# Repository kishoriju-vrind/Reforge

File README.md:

<div align="center">

# Reforge

**Custom FPGA Development Board & ESP32 Host System**

## **FRONT**

## **BACK**

</div>

## Table of Contents
* [About the Project](#about-the-project)
  * [Aim](#aim)
  * [Description](#description)
  * [Tech-Stack](#tech-stack)
* [File Structure](#file-structure)
* [Getting Started](#getting-started)
* [Usage](#usage)
  * [1. iCE40 FPGA Graphics Demo](#1-ice40-fpga-graphics-demo)
  * [2. ESP32 Host Firmware](#2-esp32-host-firmware)

---

## About the Project

### Aim
Designing a custom PCB development board that combines an ESP32 microcontroller and an iCE40 FPGA to understand how microcontrollers and FPGAs interact in real embedded systems.

### Description
Instead of relying on fixed hardware, FPGAs allow for custom hardware configurations. In this project, the **ESP32** acts as the host system. It is responsible for storing FPGA designs in its filesystem and loading them directly onto the **iCE40 FPGA** when needed. The two chips communicate via SPI, allowing the ESP32 to send data and control the FPGA dynamically. 

The current hardware prototype includes a custom VGA output implementation, where the FPGA acts as a hardwired video card rendering horizontal RGB color bands in real-time.

### Tech-Stack
* **Languages:** Embedded C (ESP32), Verilog HDL (FPGA)
* **Tools:** ESP-IDF, OSS CAD Suite (Yosys, NextPNR), KiCAD
* **Protocols:** SPI (Inter-chip communication), VGA (Analog Video),OTA 

---

## File Structure

```text
Reforge
├── ESP32E                  # ESP32 source code and firmware
│   └── OTA                 # Host system and file management
│       ├── main            # Core C files (SPI communication, FPGA config)
│       ├── CMakeLists.txt  # Build configuration
│       └── partitions.csv  # Custom memory partitions for bitstream storage
        └── README.md  
├── ICE40                   # FPGA hardware designs in Verilog
│   ├── blink               # Basic LED blink and SPI test
        ├── blink.v           # Verilog logic for horizontal RGB bands
│       ├── pins.pcf        # FPGA pinout mapping
│       ├── build.bat       # Automated synthesis script
│       └── flash.bat       # Automated flashing script
│   └── VGA                 # Custom hardware VGA generator
│       ├── vga.v           # Verilog logic for horizontal RGB bands
│       ├── pins.pcf        # FPGA pinout mapping
│       ├── build.bat       # Automated synthesis script
│       └── flash.bat       # Automated flashing script
├── KICAD                   # Schematics for the custom development board
│   ├── Reforge.kicad_sch
│   └── Reforge.kicad_pcb
└── README.md
```
## Getting Started

### Installation

Clone the repository:

```bash
git clone https://github.com/kishorju-vrind/Reforge.git
cd Reforge
```

## System Architecture & Modules

The project is divided into different functional modules. Each module handles a specific part of the system.

- **FPGA Configuration Manager:** Stores multiple FPGA designs on the ESP32 and loads them onto the iCE40 FPGA.
- **ESP32-iCE40 SPI Communication:** Handles data transfer and control between the ESP32 and iCE40 FPGA using SPI.
- **Over-The-Air (OTA) Updates:** Allows new bitstreams and firmware to be downloaded remotely over Wi-Fi.
- **Bitstream Transfer & CRC Check:** Transfers the FPGA configuration file in parts and checks the data for errors during transfer.
- **Wireless Design Selection:** Allows the user to select and load the required FPGA design remotely.

## Usage

The following steps explain how to build and run the different parts of the project.

### 1. OTA

Go to the OTA directory:

```bash
cd ESP32/OTA
```

Enter your Wi-Fi SSID and password in the required fields in the code:

```
#define WIFI_SSID "Your_SSID"
#define WIFI_PASS "Your_Password"
```
Build the project using ESP-IDF:
```
idf.py fullclean
idf.py build
```

Flash the firmware and open the serial monitor:
```
idf.py flash monitor
```

### 2.FPGA Configuration
Open the required FPGA project from the FPGA folder.
Build the Verilog design using the provided build script:
```
build.bat
```
After building, flash the generated bitstream to the iCE40 FPGA using:
```
flash.bat
```

### 3. ESP32-ICE40 SPI Communication
Open the SPI communication project from the ESP32 folder.
Build and flash the ESP32 code using:
```
idf.py build flash monitor
```
The ESP32 then communicates with the iCE40 FPGA through SPI.

### 4. bitstream Transfer and CRC Check

Run the ESP32 firmware and start the firmware/bitstream transfer.
The bitstream is transferred in smaller parts and the CRC check is used to verify the received data.
## Results
The schematic and design for the custom PCB was completed. The main communication and FPGA related functions were also tested separately.

The following results were achieved:

- ESP32-E to ESP32-E communication
- OTA communication and wireless FPGA configuration
- VGA output using the iCE40 (UPduino) FPGA

## Contributors

* [Suraj Giri](https://github.com/kishorju-vrind)
* [Amrit Tiwari](https://github.com/amrit-reboot)

## Mentors

* [Archit More](https://github.com/avm1234567)
* [Harshit Bhalani](https://github.com/harshit6-b)

## Resources

- [Generating VGA with an FPGA](https://blog.waynejohnson.net/doku.php/generating_vga_with_an_fpga)
- [FPGA and VGA Tutorial](https://youtu.be/FlkNgJXEyrc?si=HfDX1ZITgR_oPYt3)
- [FPGA Tutorial](https://www.youtube.com/watch?v=yLNWu6AxftI)
- [FPGA Learning Playlist](https://youtube.com/playlist?list=PLEBQazB0HUyQ5YJSdCBb79orXaR3Uk5vm&si=PIlAy49dysh-u-zc)
- [HDLBits Problem Sets](https://hdlbits.01xz.net/wiki/Problem_sets)
- [ESP-IDF File System Documentation](https://docs.espressif.com/projects/esp-idf/en/stable/esp32/api-guides/file-system-considerations.html)
- [ESP32 Tutorial](https://youtu.be/MCi7dCBhVpQ?si=dbMR7HTboAvRNwoI)
- [Shrike Documentation](https://vicharak-in.github.io/shrike/index.html)

## Acknowledgements

We are grateful to our mentors – **Harshit Bhalani** and **Archit More** – for their guidance and support throughout the course of this project.

We also thank [SRA-VJTI](https://sravjti.in/) for their support in organizing [Eklavya 2026](https://eklavya.sravjti.in/) and for providing us the opportunity to work on this project.

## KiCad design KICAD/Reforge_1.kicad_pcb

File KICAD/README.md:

THIS FOLDER IS MEANT TO STORE THE PCB DESIGNS, MADE ON KICAD 10.0

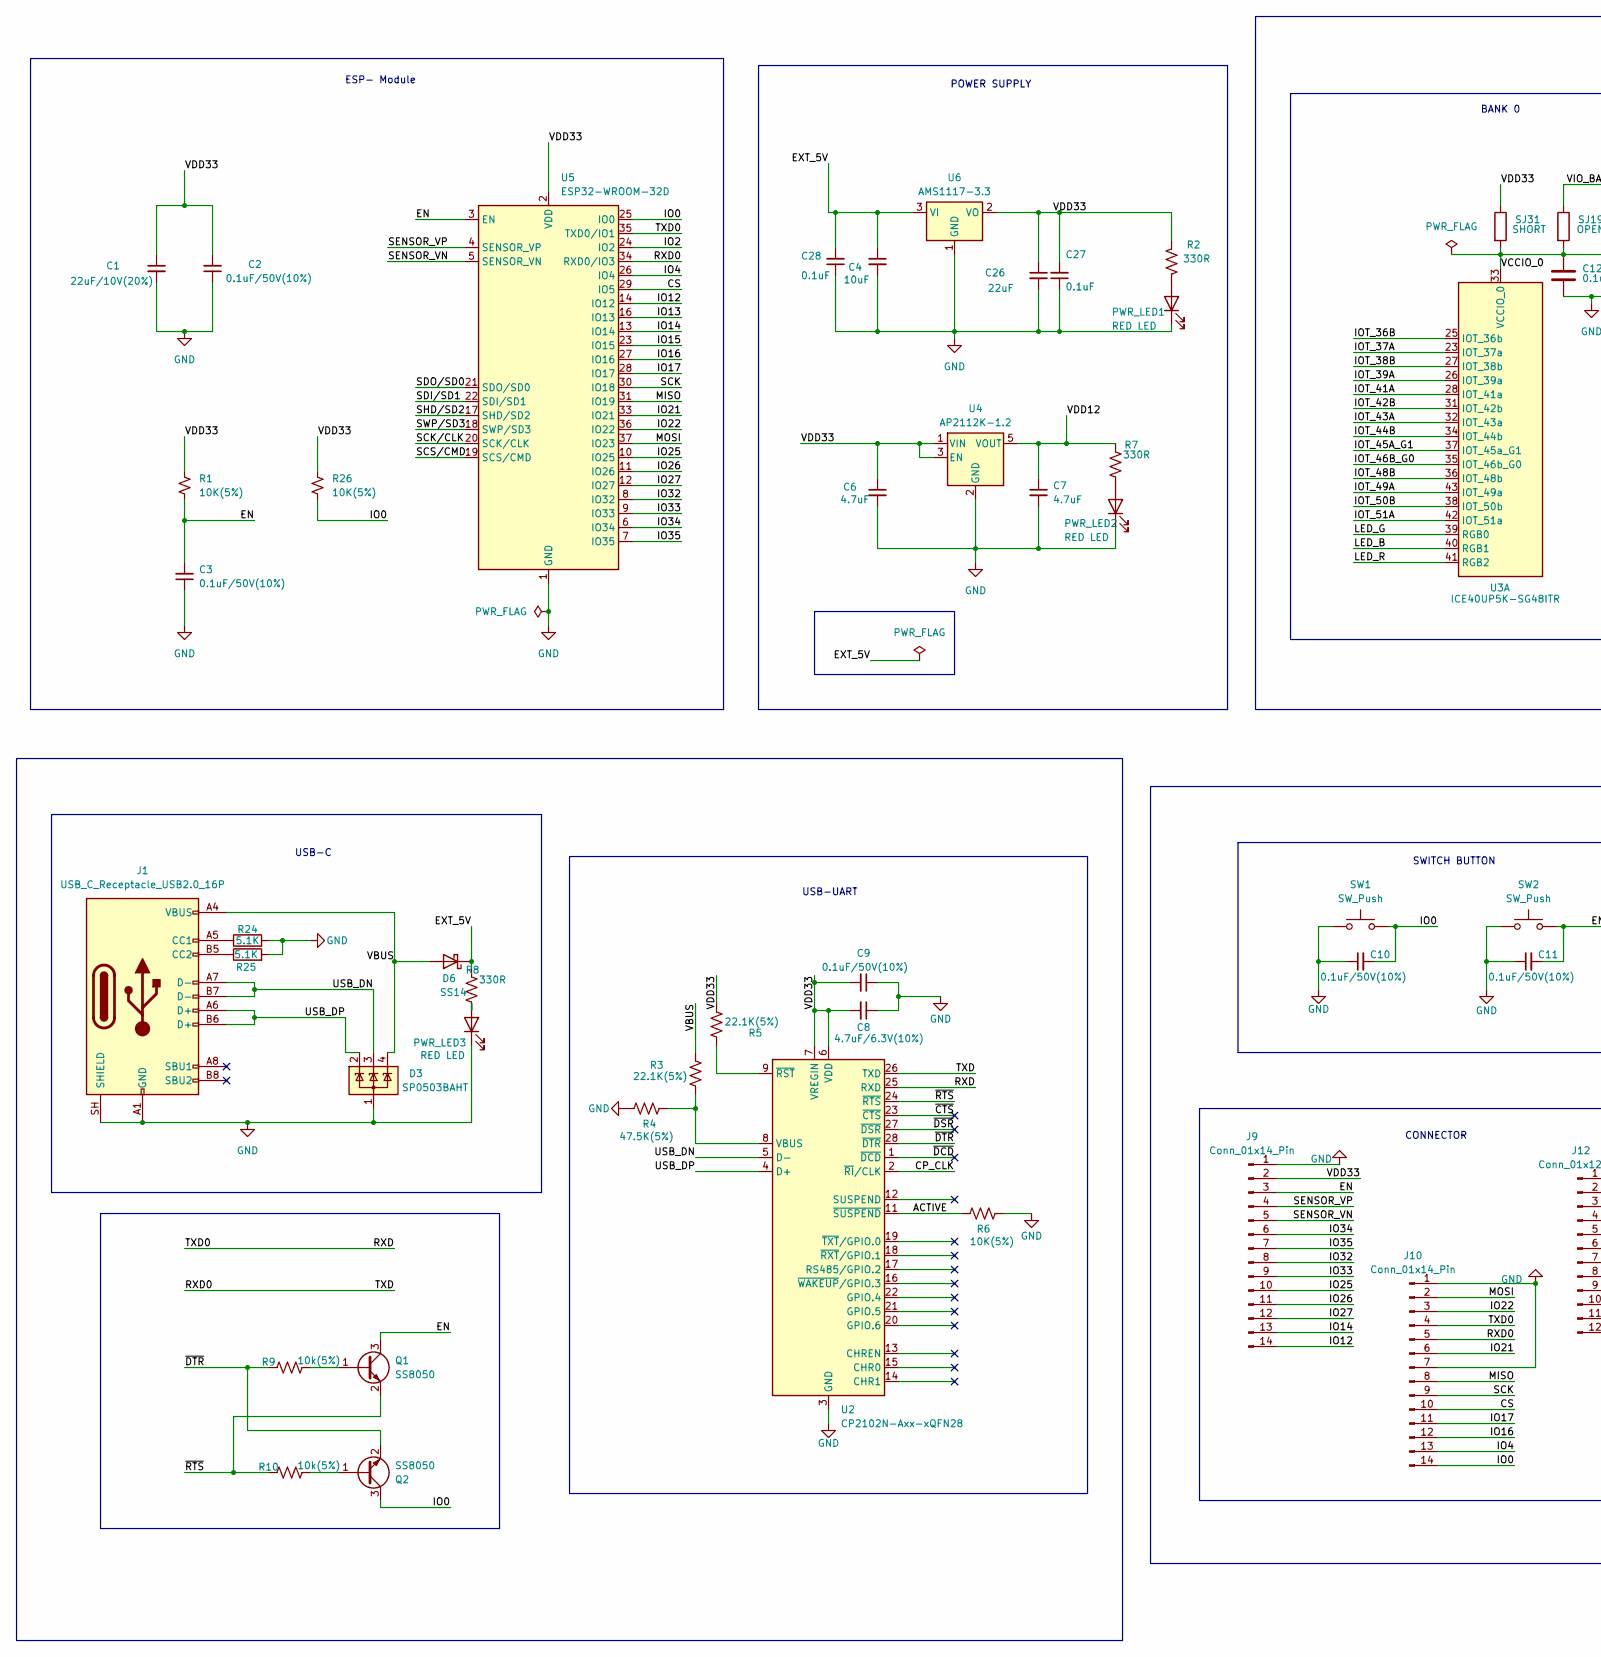
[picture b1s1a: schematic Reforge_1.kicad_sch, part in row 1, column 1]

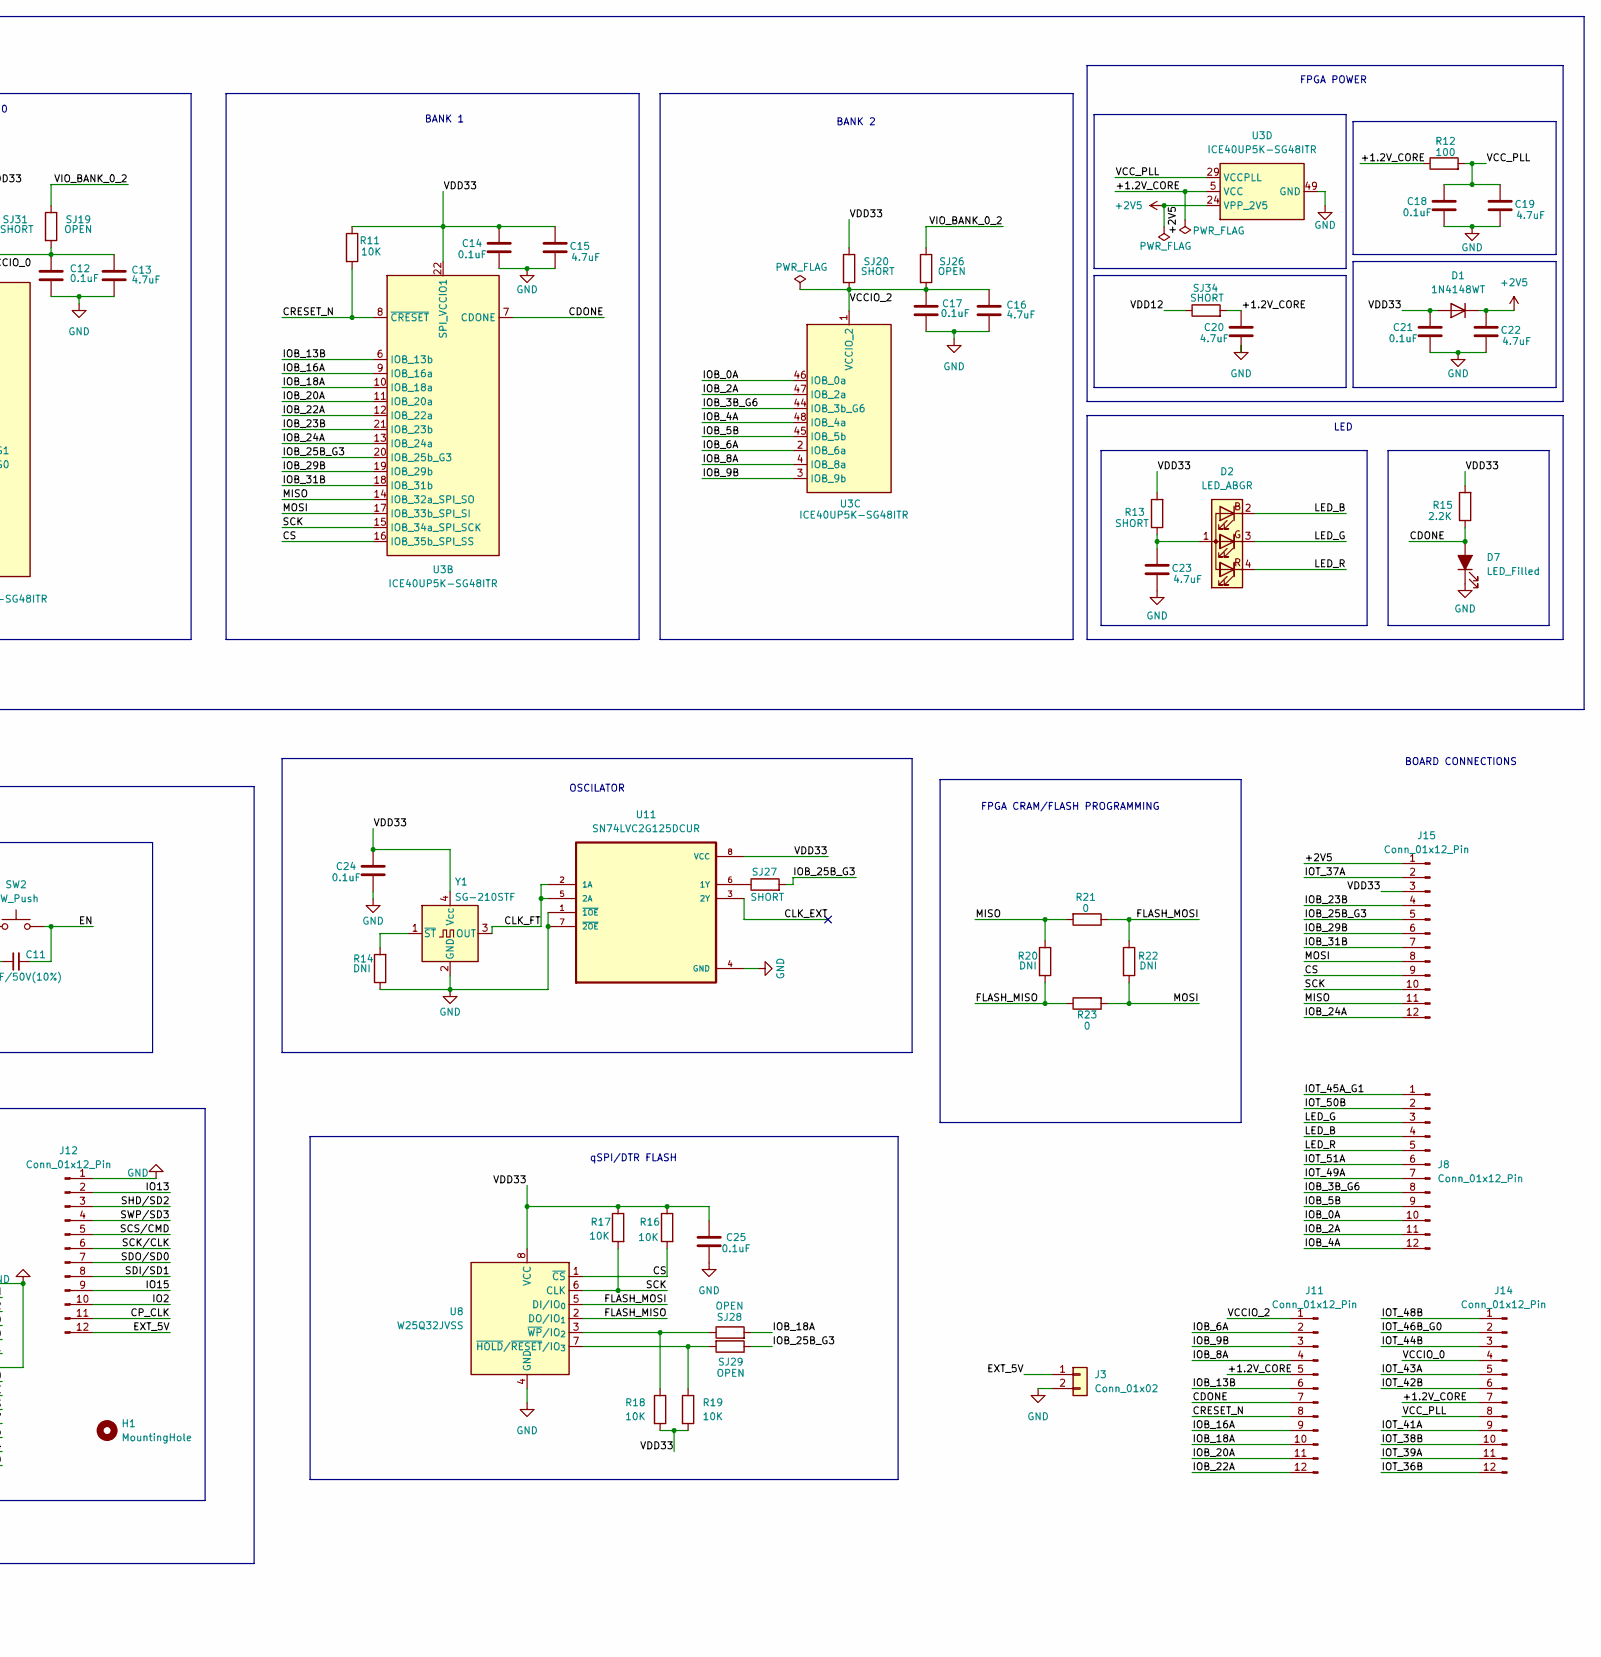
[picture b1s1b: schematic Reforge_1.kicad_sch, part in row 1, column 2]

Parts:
C1: 22uF/10V(20%); C_0805_2012Metric
C2, C3, C9, C10, C11: 0.1uF/50V(10%); C_0805_2012Metric
C4: 10uF; C_0805_2012Metric
C6, C7, C13, C15, C16, C19, C20, C22, C23: 4.7uF; C_0805_2012Metric
C8: 4.7uF/6.3V(10%); C_0805_2012Metric
C12, C14, C17, C18, C21, C24, C25, C27, C28: 0.1uF; C_0805_2012Metric
C26: 22uF; C_0805_2012Metric
D1: 1N4148WT; D_SOD-523
D2: LED_ABGR; LED_RGB_Wuerth-PLCC4_3.2x2.8mm_150141M173100
D3: SP0503BAHT; SOT-143
D6: SS14; D_SMB
D7: LED_Filled; LED_0603_1608Metric
H1: MountingHole; MountingHole_2.1mm
J1: USB_C_Receptacle_USB2.0_16P; USB_C_Receptacle_GCT_USB4105-xx-A_16P_TopMnt_Horizontal
J3: Conn_01x02; PinHeader_1x02_P2.54mm_Vertical
J8, J11, J12, J14, J15: Conn_01x12_Pin; PinHeader_1x12_P2.54mm_Vertical
J9, J10: Conn_01x14_Pin; PinHeader_1x14_P2.54mm_Vertical
PWR_LED1, PWR_LED2, PWR_LED3: RED LED; LED_0603_1608Metric
Q1, Q2: SS8050; SOT-23
R1, R6, R26: 10K(5%); R_0805_2012Metric_Pad1.20x1.40mm_HandSolder
R2, R7, R8: 330R; R_0805_2012Metric_Pad1.20x1.40mm_HandSolder
R3, R5: 22.1K(5%); R_0805_2012Metric_Pad1.20x1.40mm_HandSolder
R4: 47.5K(5%); R_0805_2012Metric_Pad1.20x1.40mm_HandSolder
R9, R10: 10k(5%); R_0805_2012Metric_Pad1.20x1.40mm_HandSolder
R11, R16, R17, R18, R19: 10K; R_0805_2012Metric_Pad1.20x1.40mm_HandSolder
R12: 100; R_0805_2012Metric_Pad1.20x1.40mm_HandSolder
R13: SHORT; SolderJumper-2_P1.3mm_Open_Pad1.0x1.5mm
R14, R20, R22: DNI; R_0805_2012Metric_Pad1.20x1.40mm_HandSolder
R15: 2.2K; R_0805_2012Metric_Pad1.20x1.40mm_HandSolder
R21, R23: 0; R_0805_2012Metric_Pad1.20x1.40mm_HandSolder
R24, R25: 5.1K; R_0805_2012Metric_Pad1.20x1.40mm_HandSolder
SJ19, SJ26, SJ28, SJ29: OPEN; SolderJumper-2_P1.3mm_Open_Pad1.0x1.5mm
SJ20, SJ31, SJ34: SHORT; SolderJumper-2_P1.3mm_Bridged2Bar_Pad1.0x1.5mm
SJ27: SHORT; SolderJumper-2_P1.3mm_Open_Pad1.0x1.5mm
SW1, SW2: SW_Push; SW_Push_SPST_NO_Alps_SKRK
U2: CP2102N-Axx-xQFN28; QFN-28-1EP_5x5mm_P0.5mm_EP3.35x3.35mm
U3: ICE40UP5K-SG48ITR; QFN-48-1EP_7x7mm_P0.5mm_EP5.6x5.6mm
U4: AP2112K-1.2; SOT-23-5
U5: ESP32-WROOM-32D
U6: AMS1117-3.3; SOT-223-3_TabPin2
U8: W25Q32JVSS; SOIC-8_5.3x5.3mm_P1.27mm
U11: SN74LVC2G125DCUR; SOP50P310X90-8N
Y1: SG-210STF; Oscillator_SMD_SeikoEpson_SG210-4Pin_2.5x2.0mm

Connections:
+2V5: C22.1, D1.1 (K), J15.1, U3.24 (VPP_2V5)
/+1.2V_CORE: C20.1, J11.5, J14.7, R12.1, SJ34.2, U3.5 (VCC), U3.30 (VCC)
/ACTIVE: R6.1, U2.11 (~SUSPEND)
/CDONE: D7.2 (A), J11.7, R15.1, U3.7 (CDONE)
/CLK_EXT: U11.3 (2Y)
/CLK_FT: U11.2 (1A), U11.5 (2A), Y1.3 (OUT)
/CP_CLK: J12.11, U2.2 (~RI/CLK)
/CRESET_N: J11.8, R11.2, U3.8 (~CRESET)
/CS: J10.10, J15.9, R16.2, U3.16 (IOB_35b_SPI_SS), U5.29 (IO5), U8.1 (~CS)
/EN: C3.2, C11.2, J9.3, Q1.3 (C), R1.2, SW2.2, U5.3 (EN)
/EXT_5V: C4.1, C28.2, D6.1 (K), J3.1, J12.12, R8.1, U6.3 (VI)
/FLASH_MISO: R20.2, R23.1, U8.2 (DO/IO_{1})
/FLASH_MOSI: R21.1, R22.1, U8.5 (DI/IO_{0})
/IO0: C10.2, J10.14, Q2.3 (C), R26.2, SW1.2, U5.25 (IO0)
/IO2: J12.10, U5.24 (IO2)
/IO4: J10.13, U5.26 (IO4)
/IO12: J9.14, U5.14 (IO12)
/IO13: J12.2, U5.16 (IO13)
/IO14: J9.13, U5.13 (IO14)
/IO15: J12.9, U5.23 (IO15)
/IO16: J10.12, U5.27 (IO16)
/IO17: J10.11, U5.28 (IO17)
/IO21: J10.6, U5.33 (IO21)
/IO22: J10.3, U5.36 (IO22)
/IO25: J9.10, U5.10 (IO25)
/IO26: J9.11, U5.11 (IO26)
/IO27: J9.12, U5.12 (IO27)
/IO32: J9.8, U5.8 (IO32)
/IO33: J9.9, U5.9 (IO33)
/IO34: J9.6, U5.6 (IO34)
/IO35: J9.7, U5.7 (IO35)
/IOB_0A: J8.10, U3.46 (IOB_0a)
/IOB_2A: J8.11, U3.47 (IOB_2a)
/IOB_3B_G6: J8.8, U3.44 (IOB_3b_G6)
/IOB_4A: J8.12, U3.48 (IOB_4a)
/IOB_5B: J8.9, U3.45 (IOB_5b)
/IOB_6A: J11.2, U3.2 (IOB_6a)
/IOB_8A: J11.4, U3.4 (IOB_8a)
/IOB_9B: J11.3, U3.3 (IOB_9b)
/IOB_13B: J11.6, U3.6 (IOB_13b)
/IOB_16A: J11.9, U3.9 (IOB_16a)
/IOB_18A: J11.10, SJ28.2, U3.10 (IOB_18a)
/IOB_20A: J11.11, U3.11 (IOB_20a)
/IOB_22A: J11.12, U3.12 (IOB_22a)
/IOB_23B: J15.4, U3.21 (IOB_23b)
/IOB_24A: J15.12, U3.13 (IOB_24a)
/IOB_25B_G3: J15.5, SJ27.2, SJ29.1, U3.20 (IOB_25b_G3)
/IOB_29B: J15.6, U3.19 (IOB_29b)
/IOB_31B: J15.7, U3.18 (IOB_31b)
/IOT_36B: J14.12, U3.25 (IOT_36b)
/IOT_37A: J15.2, U3.23 (IOT_37a)
/IOT_38B: J14.10, U3.27 (IOT_38b)
/IOT_39A: J14.11, U3.26 (IOT_39a)
/IOT_41A: J14.9, U3.28 (IOT_41a)
/IOT_42B: J14.6, U3.31 (IOT_42b)
/IOT_43A: J14.5, U3.32 (IOT_43a)
/IOT_44B: J14.3, U3.34 (IOT_44b)
/IOT_45A_G1: J8.1, U3.37 (IOT_45a_G1)
/IOT_46B_G0: J14.2, U3.35 (IOT_46b_G0)
/IOT_48B: J14.1, U3.36 (IOT_48b)
/IOT_49A: J8.7, U3.43 (IOT_49a)
/IOT_50B: J8.2, U3.38 (IOT_50b)
/IOT_51A: J8.6, U3.42 (IOT_51a)
/LED_B: D2.2 (BK), J8.4, U3.40 (RGB1)
/LED_G: D2.3 (GK), J8.3, U3.39 (RGB0)
/LED_R: D2.4 (RK), J8.5, U3.41 (RGB2)
/MISO: J10.8, J15.11, R20.1, R21.2, U3.14 (IOB_32a_SPI_SO), U5.31 (IO19)
/MOSI: J10.2, J15.8, R22.2, R23.2, U3.17 (IOB_33b_SPI_SI), U5.37 (IO23)
/RXD: J10.4, U2.25 (RXD), U5.35 (TXD0/IO1)
/RXD0: J10.5, U2.26 (TXD), U5.34 (RXD0/IO3)
/SCK: J10.9, J15.10, R17.2, U3.15 (IOB_34a_SPI_SCK), U5.30 (IO18), U8.6 (CLK)
/SCK/CLK: J12.6, U5.20 (SCK/CLK)
/SCS/CMD: J12.5, U5.19 (SCS/CMD)
/SDI/SD1: J12.8, U5.22 (SDI/SD1)
/SDO/SD0: J12.7, U5.21 (SDO/SD0)
/SENSOR_VN: J9.5, U5.5 (SENSOR_VN)
/SENSOR_VP: J9.4, U5.4 (SENSOR_VP)
/SHD/SD2: J12.3, U5.17 (SHD/SD2)
/SWP/SD3: J12.4, U5.18 (SWP/SD3)
/USB_DN: D3.3 (K), J1.A7 (D-), J1.B7 (D-), U2.5 (D-)
/USB_DP: D3.2 (K), J1.A6 (D+), J1.B6 (D+), U2.4 (D+)
/VBUS: D3.4 (K), D6.2 (A), J1.A4 (VBUS), J1.A9 (VBUS), J1.B4 (VBUS), J1.B9 (VBUS), R3.1
/VCCIO_0: C12.1, C13.1, J14.4, SJ19.2, SJ31.2, U3.33 (VCCIO_0)
/VCCIO_2: C16.1, C17.1, J11.1, SJ20.2, SJ26.2, U3.1 (VCCIO_2)
/VCC_PLL: C18.1, C19.1, J14.8, R12.2, U3.29 (VCCPLL)
/VDD12: C7.1, R7.1, SJ34.1, U4.5 (VOUT)
/VDD33: C1.1, C2.2, C6.1, C8.2, C9.2, C14.1, C15.1, C21.1, C24.1, C25.1, C26.1, C27.2, D1.2 (A), J9.2, J15.3, R1.1, R2.1, R5.2, R11.1, R13.2, R15.2, R16.1, R17.1, R18.2, R19.2, R26.1, SJ20.1, SJ31.1, U2.6 (VDD), U2.7 (VREGIN), U3.22 (SPI_VCCIO1), U4.1 (VIN), U4.3 (EN), U5.2 (VDD), U6.2 (VO), U8.8 (VCC), U11.8 (VCC), Y1.4 (Vcc)
/VIO_BANK_0_2: SJ19.1, SJ26.1
/~CTS: U2.23 (~CTS)
/~DCD: U2.1 (~DCD)
/~DSR: U2.27 (~DSR)
/~DTR: Q2.2 (E), R9.1, U2.28 (~DTR)
/~RTS: Q1.2 (E), R10.1, U2.24 (~RTS)
GND: C1.2, C2.1, C3.1, C4.2, C6.2, C7.2, C8.1, C9.1, C10.1, C11.1, C12.2, C13.2, C14.2, C15.2, C16.2, C17.2, C18.2, C19.2, C20.2, C21.2, C22.2, C23.2, C24.2, C25.2, C26.2, C27.1, C28.1, D3.1 (A), D7.1 (K), J1.A1 (GND), J1.A12 (GND), J1.B1 (GND), J1.B12 (GND), J1.SH (SHIELD), J3.2, J9.1, J10.1, J10.7, J12.1, PWR_LED1.1 (K), PWR_LED2.1 (K), PWR_LED3.1 (K), R4.1, R6.2, R14.1, R24.2, R25.2, SW1.1, SW2.1, U2.3 (GND), U2.29 (GND), U3.49 (GND), U4.2 (GND), U5.1 (GND), U5.15 (GND), U5.38 (GND), U5.39 (GND), U6.1 (GND), U8.4 (GND), U11.1 (~1OE), U11.4 (GND), U11.7 (~2OE), Y1.2 (GND)
unnamed: C23.1, D2.1 (A), R13.1
unnamed: J1.A5 (CC1), R24.1
unnamed: J1.B5 (CC2), R25.1
unnamed: PWR_LED1.2 (A), R2.2
unnamed: PWR_LED2.2 (A), R7.2
unnamed: PWR_LED3.2 (A), R8.2
unnamed: Q1.1 (B), R9.2
unnamed: Q2.1 (B), R10.2
unnamed: R3.2, R4.2, U2.8 (VBUS)
unnamed: R5.1, U2.9 (~RST)
unnamed: R19.1, SJ29.2, U8.7 (~HOLD/~RESET/IO_{3})
unnamed: R18.1, SJ28.1, U8.3 (~WP/IO_{2})
unnamed: SJ27.1, U11.6 (1Y)
unnamed: R14.2, Y1.1 (~ST)

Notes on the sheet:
BANK 0
USB-UART
CONNECTOR
LED
POWER SUPPLY
OSCILATOR
SWITCH BUTTON
USB-C
BANK 2
BANK 1
FPGA CRAM/FLASH PROGRAMMING
BOARD CONNECTIONS
FPGA POWER
ESP- Module
qSPI/DTR FLASH

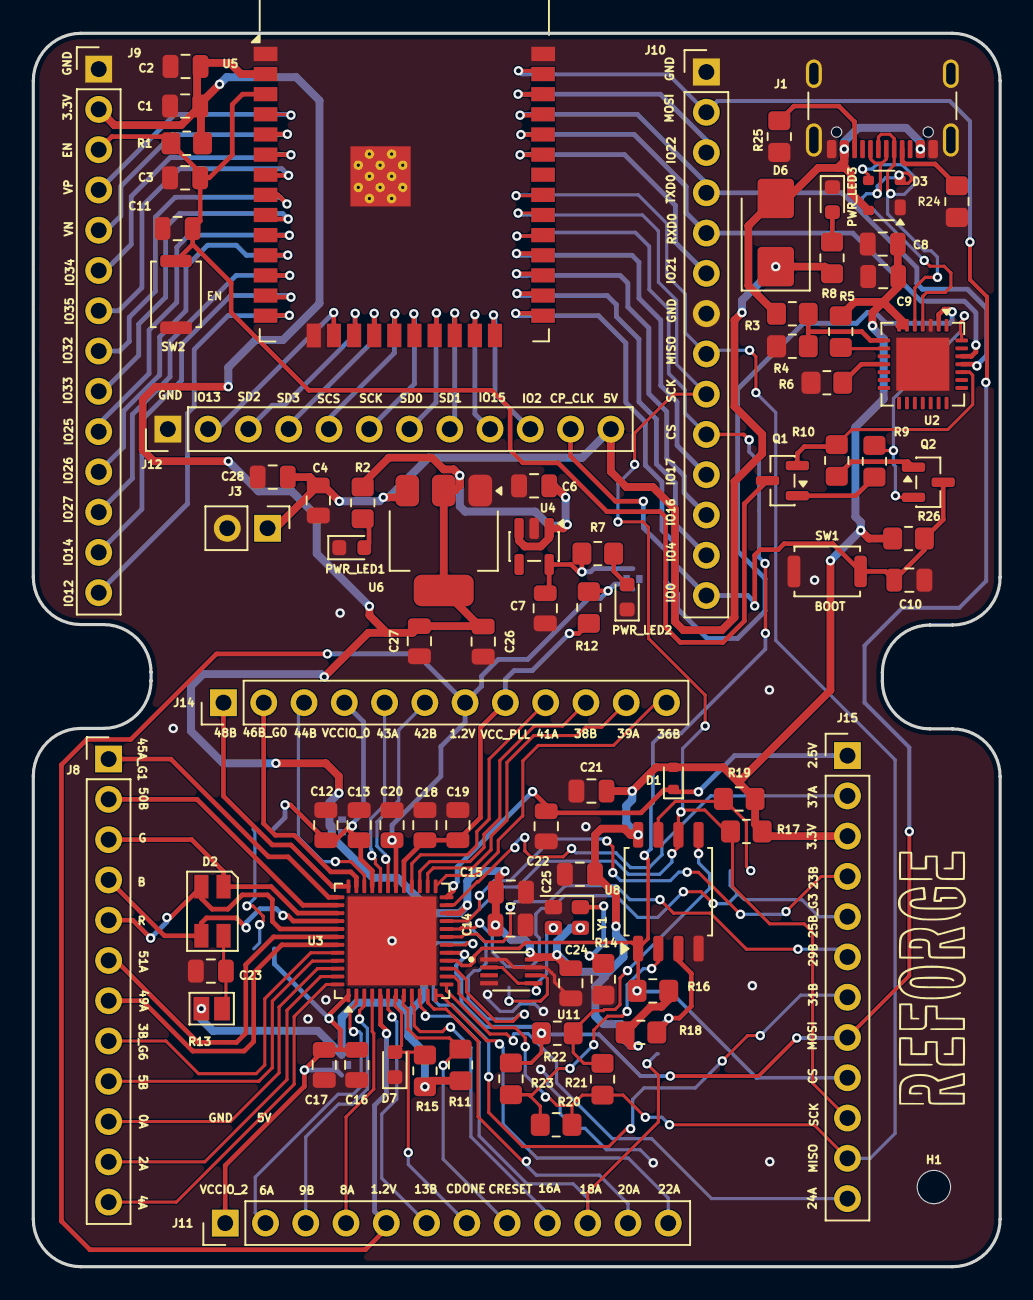
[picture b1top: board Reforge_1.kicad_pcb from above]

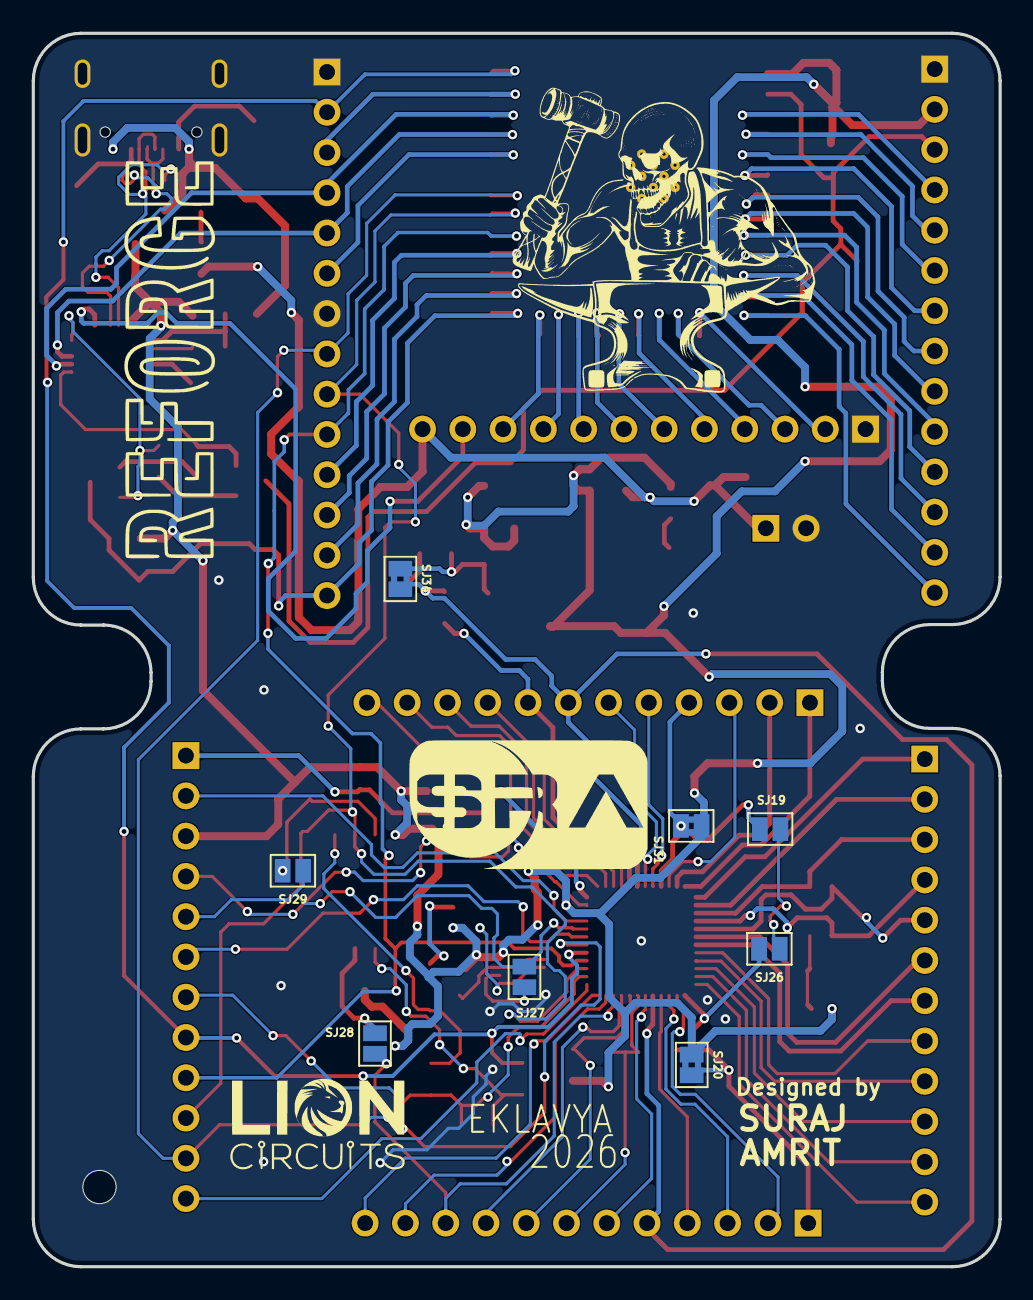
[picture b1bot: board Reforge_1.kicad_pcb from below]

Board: 2 copper layers, 61.0 x 77.8 mm, 91 parts (8 on the bottom side), 104 nets.
